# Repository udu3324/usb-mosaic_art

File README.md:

# usb-mosaic_art

A simple and fun gadget pcb

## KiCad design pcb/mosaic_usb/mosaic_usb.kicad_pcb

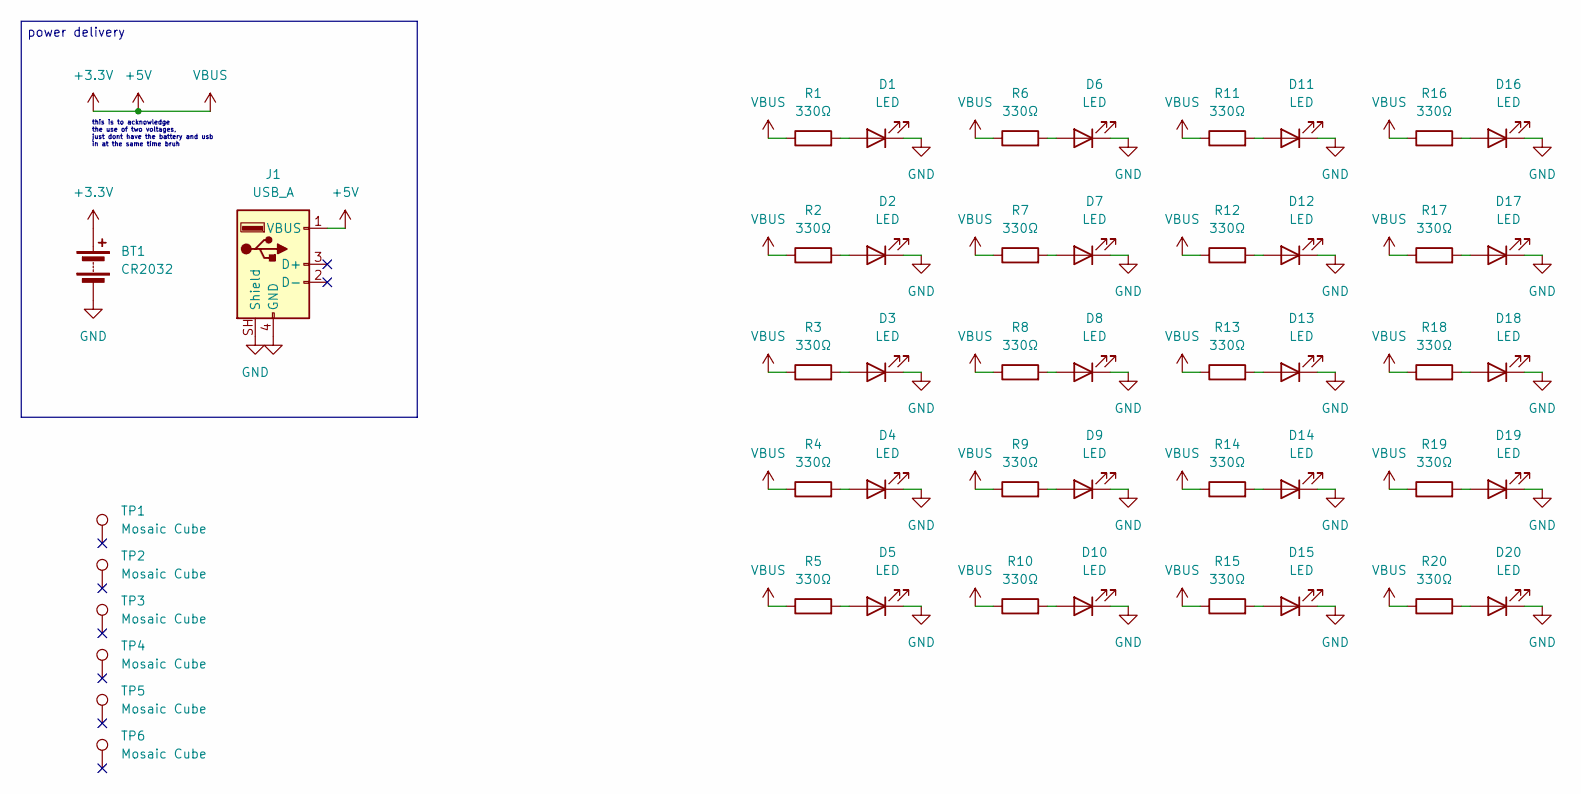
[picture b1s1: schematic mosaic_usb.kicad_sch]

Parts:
BT1: CR2032; BATT_HLDR_LNX
D1, D2, D3, D4, D5, D6, D7, D8, D9, D10, D11, D12, D13, D14, D15, D16, D17, D18, D19, D20: LED; LED_D3.0mm_Clear_Sideways_Hack
J1: USB_A; USB_A_PCB_Edge_receptacle
R1, R2, R3, R4, R5, R6, R7, R8, R9, R10, R11, R12, R13, R14, R15, R16, R17, R18, R19, R20: 330Ω; R_0603_1608Metric
TP1, TP2, TP3, TP4, TP5, TP6: Mosaic Cube; Mosaic Copper Cube

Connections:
+3.3V: BT1.1 (+), J1.1 (VBUS), R1.1, R2.1, R3.1, R4.1, R5.1, R6.1, R7.1, R8.1, R9.1, R10.1, R11.1, R12.1, R13.1, R14.1, R15.1, R16.1, R17.1, R18.1, R19.1, R20.1
GND: BT1.2 (-), D1.1 (K), D2.1 (K), D3.1 (K), D4.1 (K), D5.1 (K), D6.1 (K), D7.1 (K), D8.1 (K), D9.1 (K), D10.1 (K), D11.1 (K), D12.1 (K), D13.1 (K), D14.1 (K), D15.1 (K), D16.1 (K), D17.1 (K), D18.1 (K), D19.1 (K), D20.1 (K), J1.4 (GND), J1.SH (Shield)
unnamed: D1.2 (A), R1.2
unnamed: D2.2 (A), R2.2
unnamed: D3.2 (A), R3.2
unnamed: D4.2 (A), R4.2
unnamed: D5.2 (A), R5.2
unnamed: D6.2 (A), R6.2
unnamed: D7.2 (A), R7.2
unnamed: D8.2 (A), R8.2
unnamed: D9.2 (A), R9.2
unnamed: D10.2 (A), R10.2
unnamed: D11.2 (A), R11.2
unnamed: D12.2 (A), R12.2
unnamed: D13.2 (A), R13.2
unnamed: D14.2 (A), R14.2
unnamed: D15.2 (A), R15.2
unnamed: D16.2 (A), R16.2
unnamed: D17.2 (A), R17.2
unnamed: D18.2 (A), R18.2
unnamed: D19.2 (A), R19.2
unnamed: D20.2 (A), R20.2

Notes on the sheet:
this is to acknowledge the use of two voltages, just dont have the battery and usb in at the same time bruh
power delivery

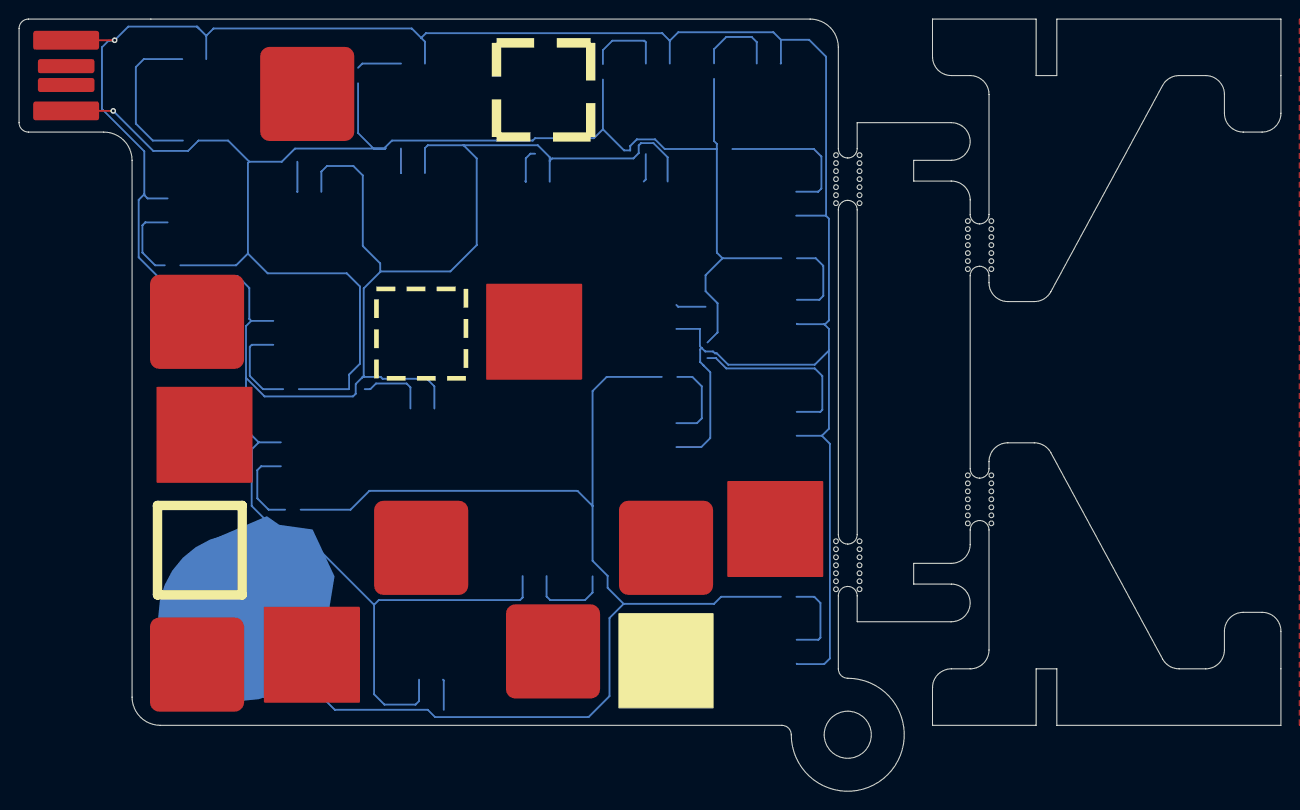
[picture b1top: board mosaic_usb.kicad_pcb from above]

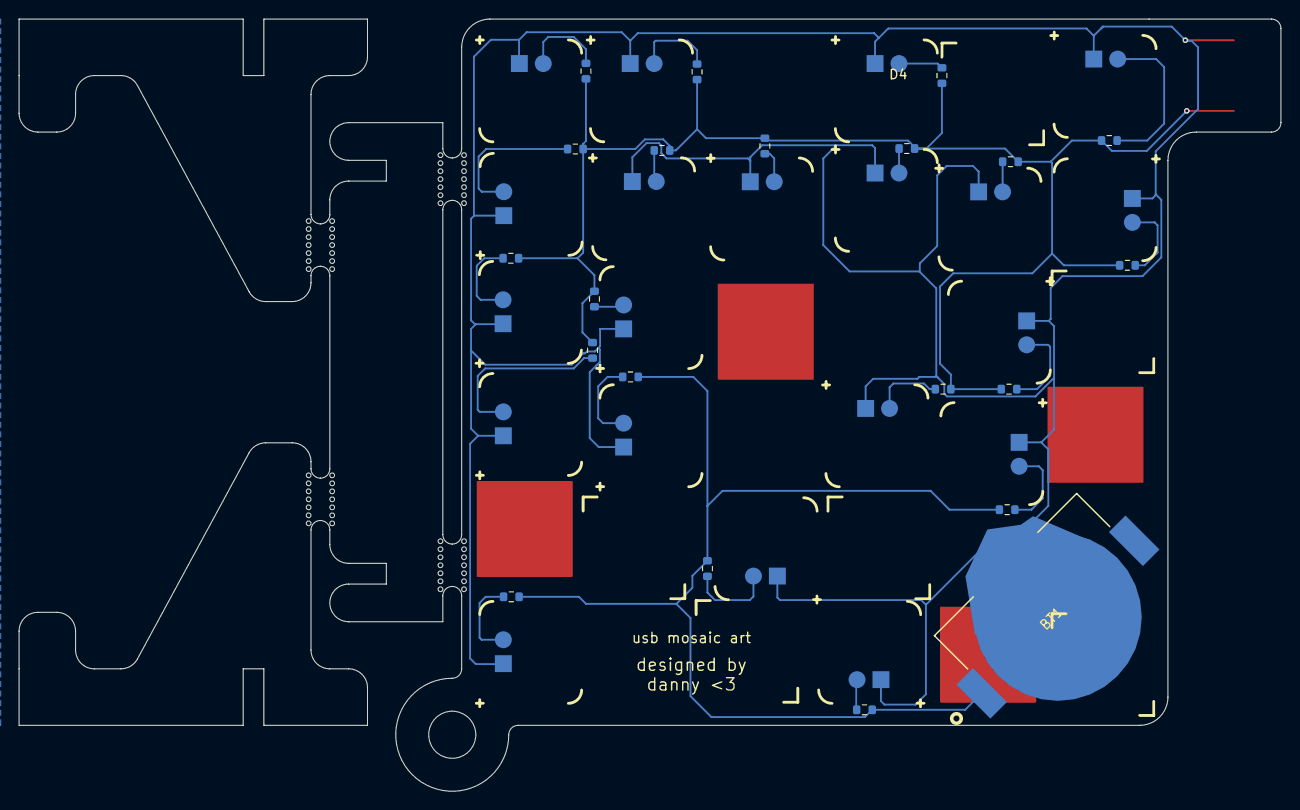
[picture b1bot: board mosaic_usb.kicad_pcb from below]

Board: 2 copper layers, 134.0 x 82.0 mm, 48 parts (41 on the bottom side), 22 nets.

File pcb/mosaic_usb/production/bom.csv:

Designator,Footprint,Quantity,Value,LCSC Part #
BT1,BATT_HLDR_LNX,1,CR2032,
"D1, D10, D11, D12, D13, D14, D15, D16, D17, D18, D19, D2, D20, D3, D4, D5, D6, D7, D8, D9",LED_D3.0mm_Clear_Sideways_Hack,20,LED,
J1,USB_A_PCB_Edge_receptacle,1,USB_A,
"R1, R10, R11, R12, R13, R14, R15, R16, R17, R18, R19, R2, R20, R3, R4, R5, R6, R7, R8, R9",0603,20,330Ω,
"TP1, TP2, TP3, TP4, TP5, TP6",Mosaic Copper Cube,6,Mosaic Cube,
